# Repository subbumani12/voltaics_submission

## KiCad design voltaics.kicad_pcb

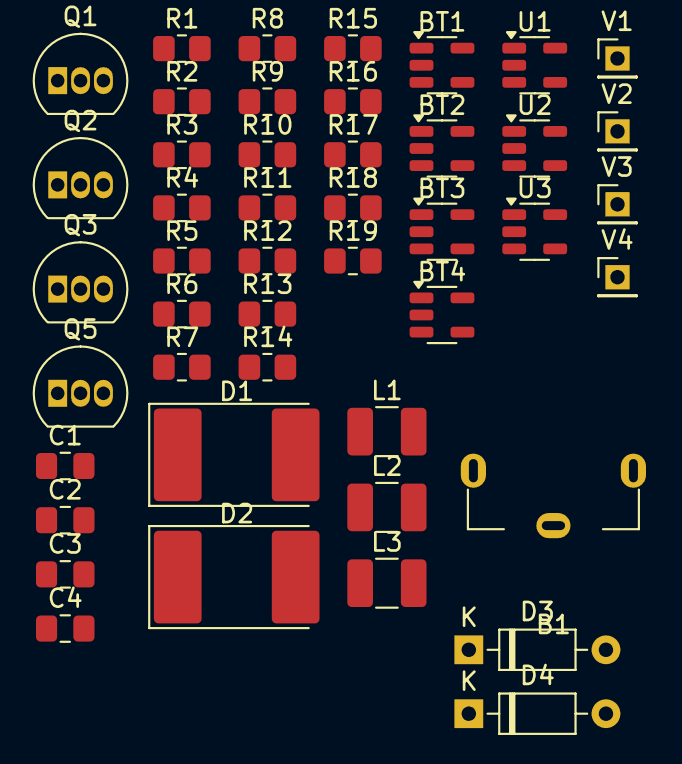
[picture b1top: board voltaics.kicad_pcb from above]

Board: 2 copper layers, 46 parts (0 on the bottom side), 28 nets, no tracks yet.

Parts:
B1: BSOURCE; BatteryHolder_Keystone_590
BT1, BT3: 12V; TSOT-23-5
BT2, BT4: -12V; TSOT-23-5
C1: 560n; C_0805_2012Metric_Pad1.18x1.45mm_HandSolder
C2: 0.01u; C_0805_2012Metric_Pad1.18x1.45mm_HandSolder
C3: 1u; C_0805_2012Metric_Pad1.18x1.45mm_HandSolder
C4: 220u; C_0805_2012Metric_Pad1.18x1.45mm_HandSolder
D1, D2: 1N1418; D_3220_8050Metric_Pad2.65x5.15mm_HandSolder
D3, D4: 1N4148; D_DO-35_SOD27_P7.62mm_Horizontal
L1, L2: 1m; L_1210_3225Metric_Pad1.42x2.65mm_HandSolder
L3: 130m; L_1210_3225Metric_Pad1.42x2.65mm_HandSolder
Q1, Q2: 2N3904; TO-92_Inline
Q3: 2N3906; TO-92_Inline
Q5: BC547; TO-92_Inline
R1, R2: 50; R_0805_2012Metric_Pad1.20x1.40mm_HandSolder
R3, R7: 10k; R_0805_2012Metric_Pad1.20x1.40mm_HandSolder
R4: 6.8k; R_0805_2012Metric_Pad1.20x1.40mm_HandSolder
R5: 22k; R_0805_2012Metric_Pad1.20x1.40mm_HandSolder
R6: 1k; R_0805_2012Metric_Pad1.20x1.40mm_HandSolder
R8: 200; R_0805_2012Metric_Pad1.20x1.40mm_HandSolder
R9, R10, R11, R12: 100; R_0805_2012Metric_Pad1.20x1.40mm_HandSolder
R13, R15: 220k; R_0805_2012Metric_Pad1.20x1.40mm_HandSolder
R14, R18: 4.7k; R_0805_2012Metric_Pad1.20x1.40mm_HandSolder
R16: 100k; R_0805_2012Metric_Pad1.20x1.40mm_HandSolder
R17: 27k; R_0805_2012Metric_Pad1.20x1.40mm_HandSolder
R19: 5000k; R_0805_2012Metric_Pad1.20x1.40mm_HandSolder
U1, U2, U3: OPA188xxDBV; TSOT-23-5
V1, V2, V3, V4: VSIN; PinHeader_1x01_P2.00mm_Vertical

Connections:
+12V: C2.1, L3.1, Q2.3 (C), R5.1, R13.1, R15.1, U1.5 (V+)
-12V: Q3.1 (E), U1.2 (V-)
GND: BT1.2 (-), BT2.1 (+), BT3.2 (-), BT4.1 (+), C4.1, L1.2, L2.2, R2.2, R4.1, R7.2, R14.2, R16.2, R19.2, U2.4 (-), U3.4 (-)
unnamed: BT1.1 (+), U2.5 (V+)
unnamed: BT2.2 (-), U2.2 (V-)
unnamed: BT3.1 (+), U3.5 (V+)
unnamed: BT4.2 (-), U3.2 (V-)
unnamed: C1.1, L1.1, R1.1
unnamed: D1.2 (A), D2.1 (K), U2.1
unnamed: D1.1 (K), R9.2, R10.1, U2.3 (+)
unnamed: D2.2 (A), R10.2, R11.1
unnamed: D3.2 (A), Q1.1 (E), R16.1
unnamed: C4.2, D3.1 (K), R17.2
unnamed: D4.2 (A), R18.2
unnamed: D4.1 (K), Q1.3 (C), R15.2
unnamed: C3.1, Q1.2 (B), R13.2, R14.1
unnamed: Q2.2 (B), R18.1
unnamed: Q3.2 (B), R17.1
unnamed: Q5.2 (B), R4.2, R5.2, R6.2
unnamed: C2.2, C3.2, L3.2, Q5.1 (C), R7.1
unnamed: Q5.3 (E), R3.1
unnamed: R1.2, V1.1
unnamed: R6.1, V2.1
unnamed: R3.2, R12.2, U3.1
unnamed: R2.1, R8.1, R9.1, U1.1, U1.3 (+)
unnamed: C1.2, L2.1, U1.4 (-)
unnamed: R8.2, R11.2, R12.1, U3.3 (+)
Vout: Q2.1 (E), Q3.3 (C), R19.1
